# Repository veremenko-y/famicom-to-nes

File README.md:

# Famicom to NES adapter

Adapter from Famicom to NES.

CIC replica chip firmware can be found at [krizz/avrciczz](https://github.com/krikzz/avrciczz).

## PCB Warning

**Board thickness must be 1.2mm**, not standard 1.6mm. **Boards over 1.2mm will damage NES ZIF cartridge socket.**

**I have not personally tested the board, [but another github user did](https://github.com/veremenko-y/famicom-to-nes/issues/1#issuecomment-1863692287)**

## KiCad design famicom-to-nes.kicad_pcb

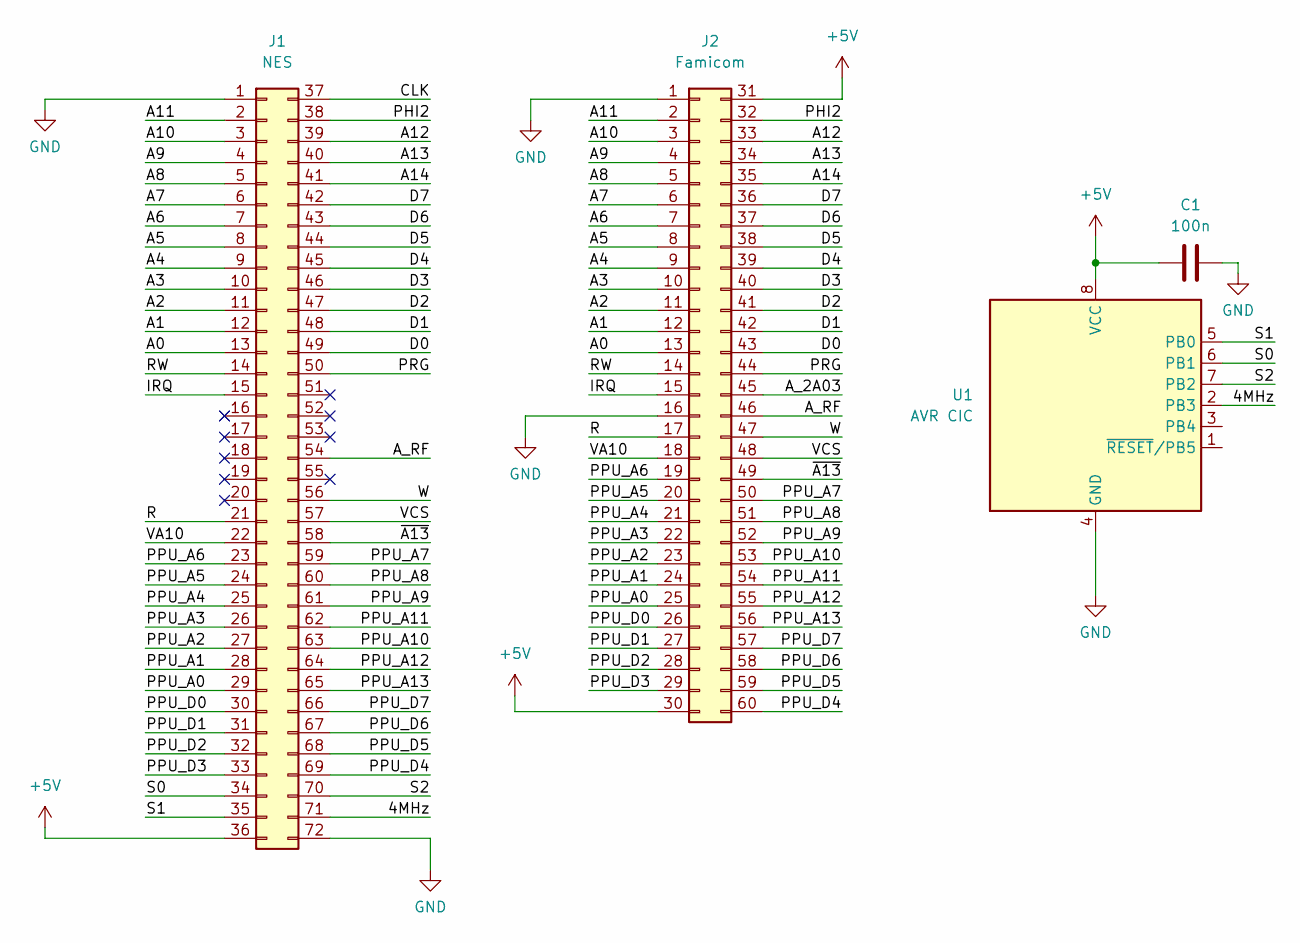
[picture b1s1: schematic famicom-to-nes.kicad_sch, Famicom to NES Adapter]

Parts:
C1: 100n; C_Disc_D4.3mm_W1.9mm_P5.00mm
J1: NES; NES_Cart_Edge_Connector
J2: Famicom; Famicom-60SocketEdge
U1: AVR CIC; DIP-8_W7.62mm

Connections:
+5V: C1.1, J1.36, J2.30, J2.31, U1.8 (VCC)
/4MHz: J1.71, U1.2 (PB3)
/A0: J1.13, J2.13
/A1: J1.12, J2.12
/A2: J1.11, J2.11
/A3: J1.10, J2.10
/A4: J1.9, J2.9
/A5: J1.8, J2.8
/A6: J1.7, J2.7
/A7: J1.6, J2.6
/A8: J1.5, J2.5
/A9: J1.4, J2.4
/A10: J1.3, J2.3
/A11: J1.2, J2.2
/A12: J1.39, J2.33
/A13: J1.40, J2.34
/A14: J1.41, J2.35
/A_2A03: J2.45
/A_RF: J1.54, J2.46
/CLK: J1.37
/D0: J1.49, J2.43
/D1: J1.48, J2.42
/D2: J1.47, J2.41
/D3: J1.46, J2.40
/D4: J1.45, J2.39
/D5: J1.44, J2.38
/D6: J1.43, J2.37
/D7: J1.42, J2.36
/IRQ: J1.15, J2.15
/PHI2: J1.38, J2.32
/PPU_A0: J1.29, J2.25
/PPU_A1: J1.28, J2.24
/PPU_A2: J1.27, J2.23
/PPU_A3: J1.26, J2.22
/PPU_A4: J1.25, J2.21
/PPU_A5: J1.24, J2.20
/PPU_A6: J1.23, J2.19
/PPU_A7: J1.59, J2.50
/PPU_A8: J1.60, J2.51
/PPU_A9: J1.61, J2.52
/PPU_A10: J1.63, J2.53
/PPU_A11: J1.62, J2.54
/PPU_A12: J1.64, J2.55
/PPU_A13: J1.65, J2.56
/PPU_D0: J1.30, J2.26
/PPU_D1: J1.31, J2.27
/PPU_D2: J1.32, J2.28
/PPU_D3: J1.33, J2.29
/PPU_D4: J1.69, J2.60
/PPU_D5: J1.68, J2.59
/PPU_D6: J1.67, J2.58
/PPU_D7: J1.66, J2.57
/PRG: J1.50, J2.44
/R: J1.21, J2.17
/RW: J1.14, J2.14
/S0: J1.34, U1.6 (PB1)
/S1: J1.35, U1.5 (PB0)
/S2: J1.70, U1.7 (PB2)
/VA10: J1.22, J2.18
/VCS: J1.57, J2.48
/W: J1.56, J2.47
/~A13: J1.58, J2.49
GND: C1.2, J1.1, J1.72, J2.1, J2.16, U1.4 (GND)

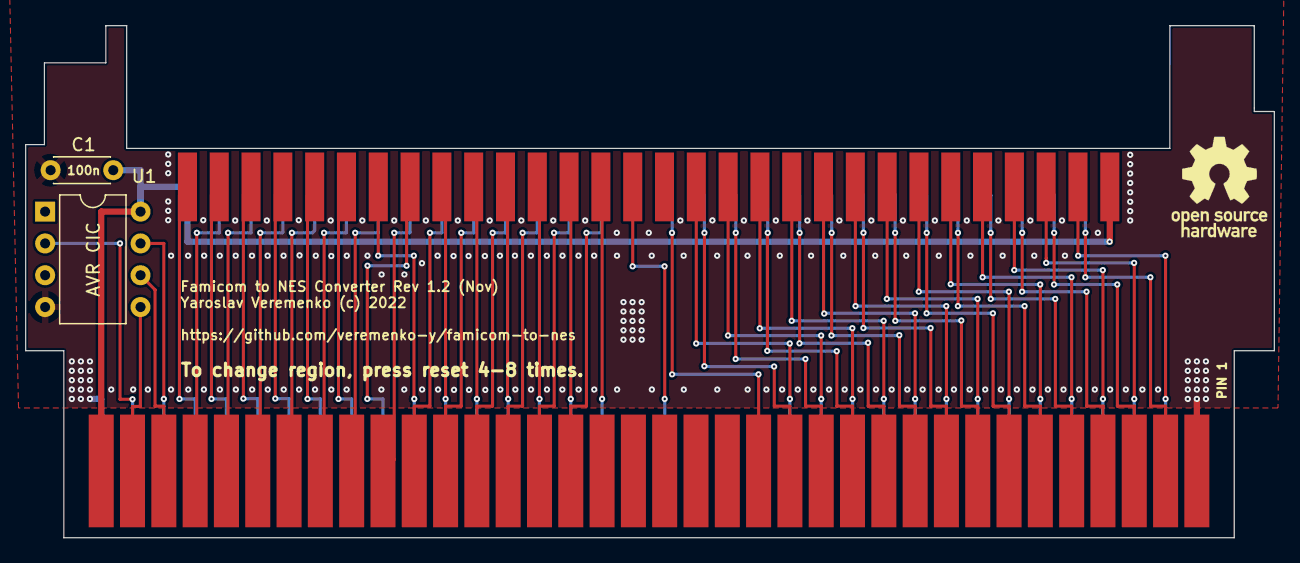
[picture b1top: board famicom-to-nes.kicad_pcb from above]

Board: 2 copper layers, 99.7 x 40.9 mm, 4 parts (1 on the bottom side), 61 nets.

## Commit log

2022-11-17 Initial commit Rev 1.1
2022-11-18 Rev 1.2

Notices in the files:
famicom-to-nes.kicad_pcb:
Yaroslav Veremenko (c) 2022
